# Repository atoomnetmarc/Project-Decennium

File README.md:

# Status

Assembled and working.

# Firmware

Flash the firmware: https://github.com/atoomnetmarc/Project-Decennium-Firmware

# Build

Order components mentioned on the [BOM](Kicad/bom/ibom.html). For the `Wemos D1 mini usb-c` (U1) you need 2 pieces of 1x08 right angle 2.54mm pin header.

Order PCB. You may want to check the option remove the order number from the front of the PCB.

Solder the PCB.

# 3d-print

3d-print a [stand](3d-print/Project-Decennium%20PCB%20stand.stl). Orient the print for printing like [this](3d-print/Project-Decennium%20PCB%20stand%20-%20print%20orientation%20example.png).

Use 2 M3x12 BHCS screws to screw the stand to the pcb.

# Pics

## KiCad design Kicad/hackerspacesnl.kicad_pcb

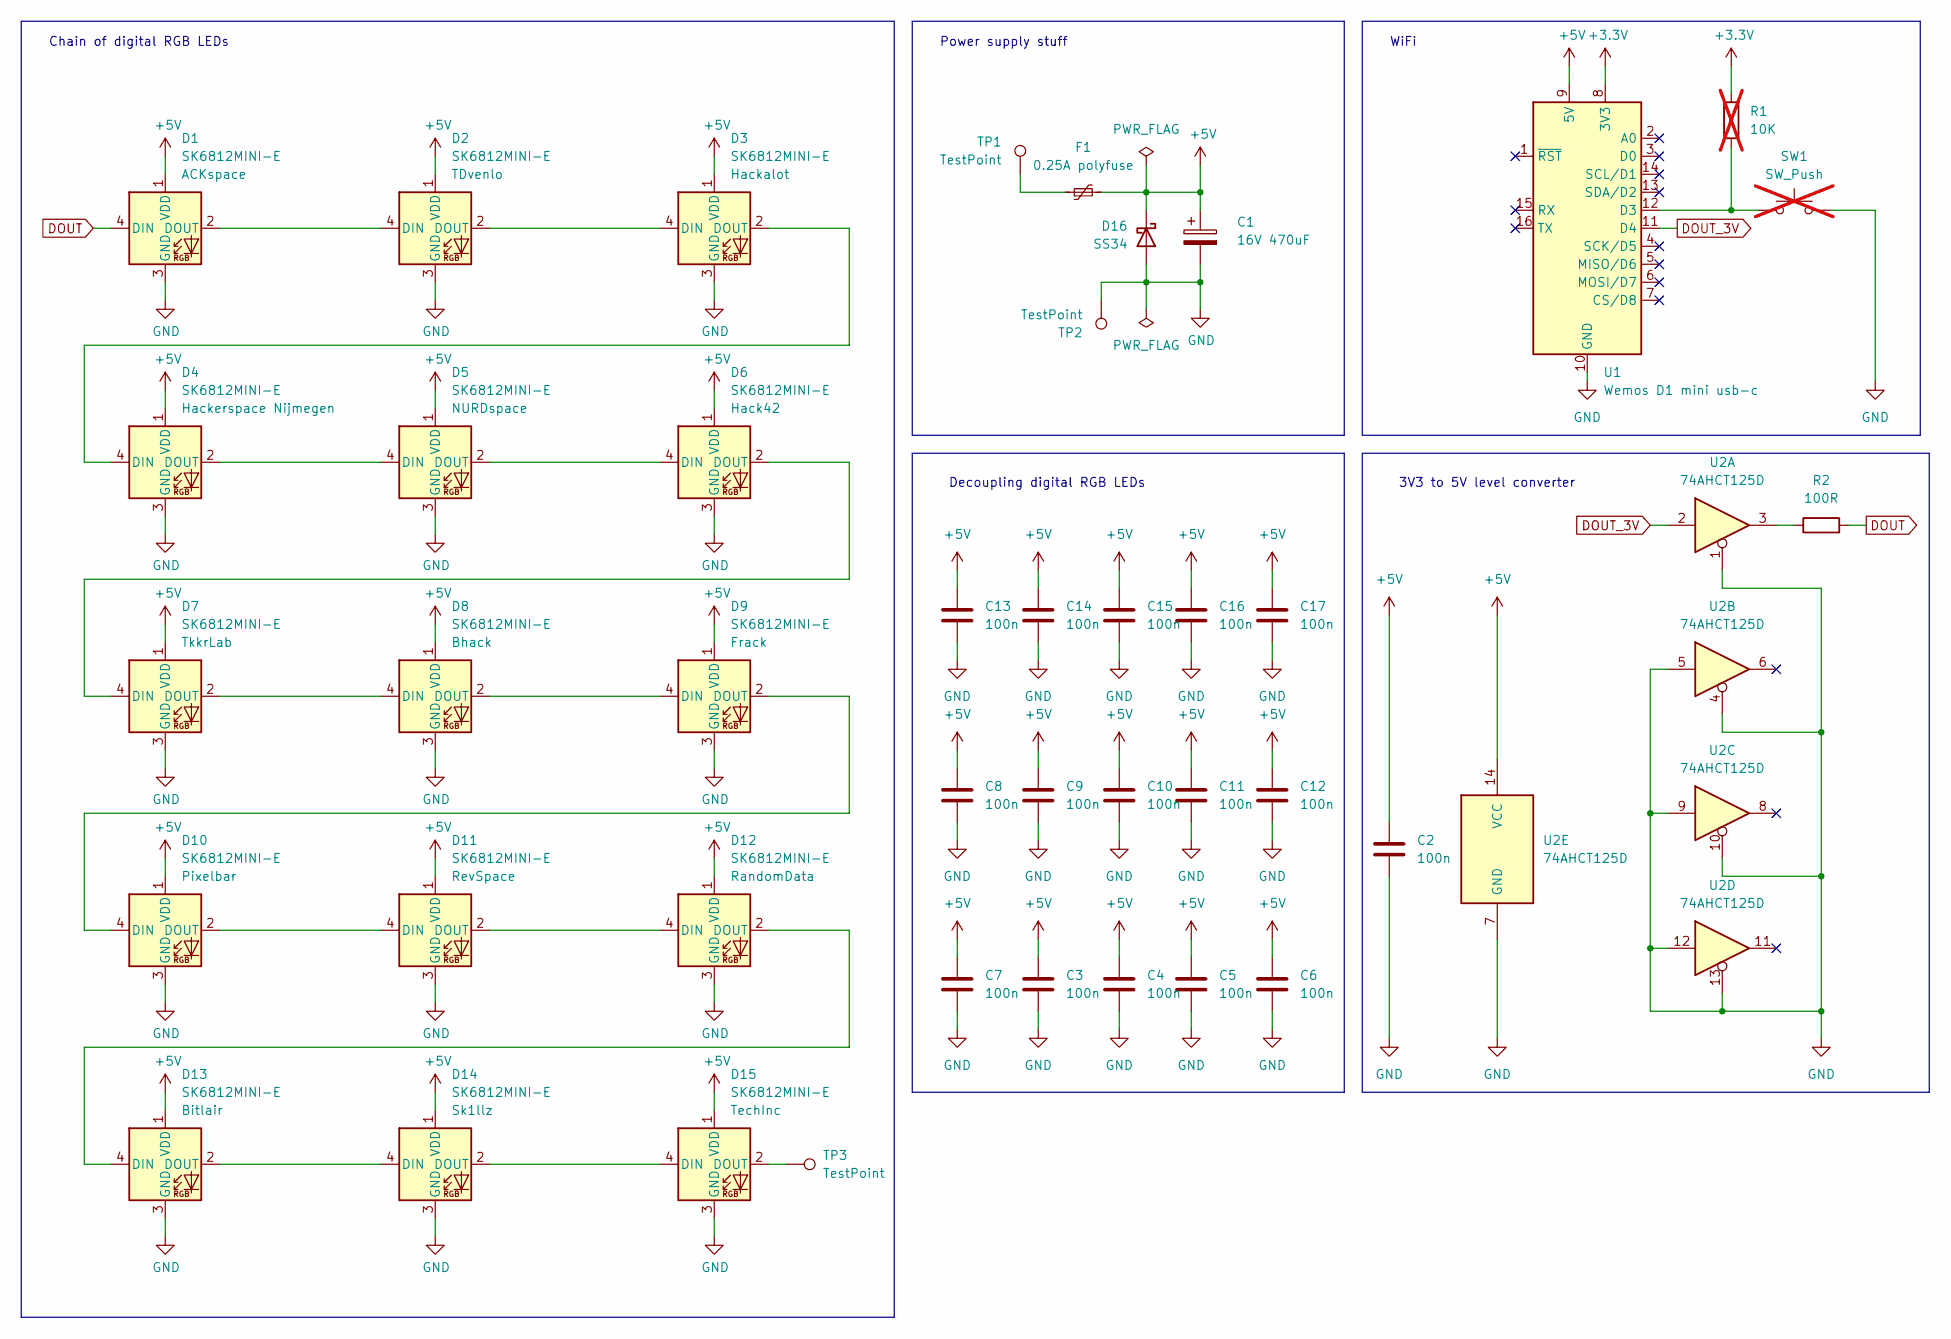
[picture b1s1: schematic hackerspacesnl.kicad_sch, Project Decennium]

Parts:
C1: 16V 470uF; CP_Elec_10x10.5
C2, C3, C4, C5, C6, C7, C8, C9, C10, C11, C12, C13, C14, C15, C16, C17: 100n; C_0805_2012Metric_Pad1.18x1.45mm_HandSolder
D1, D2, D3, D4, D5, D6, D7, D8, D9, D10, D11, D12, D13, D14, D15: SK6812MINI-E; LED_SK6812MINI-E_3.2x2.8x1.78mm_P1.5mm; LCSC C391863
D16: SS34; D_SMA
F1: 0.25A polyfuse; Fuse_1206_3216Metric_Pad1.42x1.75mm_HandSolder
R1: 10K; R_0805_2012Metric_Pad1.20x1.40mm_HandSolder; not fitted
R2: 100R; R_0805_2012Metric_Pad1.20x1.40mm_HandSolder
SW1: SW_Push; SW_SPST_CK_RS282G05A3; not fitted
TP1, TP2: TestPoint; TestPoint_Pad_D4.0mm
TP3: TestPoint; TestPoint_Pad_D1.5mm
U1: Wemos D1 mini usb-c; WEMOS_D1_mini_smt_hack
U2: 74AHCT125D; SOIC-14_3.9x8.7mm_P1.27mm

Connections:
+3.3V: R1.2, U1.8 (3V3)
+5V: C1.1, C2.1, C3.1, C4.1, C5.1, C6.1, C7.1, C8.1, C9.1, C10.1, C11.1, C12.1, C13.1, C14.1, C15.1, C16.1, C17.1, D1.1 (VDD), D2.1 (VDD), D3.1 (VDD), D4.1 (VDD), D5.1 (VDD), D6.1 (VDD), D7.1 (VDD), D8.1 (VDD), D9.1 (VDD), D10.1 (VDD), D11.1 (VDD), D12.1 (VDD), D13.1 (VDD), D14.1 (VDD), D15.1 (VDD), D16.1 (K), F1.2, U1.9 (5V), U2.14 (VCC)
DOUT: D1.4 (DIN), R2.2
DOUT_3V: U1.11 (D4), U2.2
GND: C1.2, C2.2, C3.2, C4.2, C5.2, C6.2, C7.2, C8.2, C9.2, C10.2, C11.2, C12.2, C13.2, C14.2, C15.2, C16.2, C17.2, D1.3 (GND), D2.3 (GND), D3.3 (GND), D4.3 (GND), D5.3 (GND), D6.3 (GND), D7.3 (GND), D8.3 (GND), D9.3 (GND), D10.3 (GND), D11.3 (GND), D12.3 (GND), D13.3 (GND), D14.3 (GND), D15.3 (GND), D16.2 (A), SW1.1, TP2.1, U1.10 (GND), U2.1, U2.4, U2.5, U2.7 (GND), U2.9, U2.10, U2.12, U2.13
unnamed: D1.2 (DOUT), D2.4 (DIN)
unnamed: D2.2 (DOUT), D3.4 (DIN)
unnamed: D3.2 (DOUT), D4.4 (DIN)
unnamed: D4.2 (DOUT), D5.4 (DIN)
unnamed: D5.2 (DOUT), D6.4 (DIN)
unnamed: D6.2 (DOUT), D7.4 (DIN)
unnamed: D7.2 (DOUT), D8.4 (DIN)
unnamed: D8.2 (DOUT), D9.4 (DIN)
unnamed: D9.2 (DOUT), D10.4 (DIN)
unnamed: D10.2 (DOUT), D11.4 (DIN)
unnamed: D11.2 (DOUT), D12.4 (DIN)
unnamed: D12.2 (DOUT), D13.4 (DIN)
unnamed: D13.2 (DOUT), D14.4 (DIN)
unnamed: D14.2 (DOUT), D15.4 (DIN)
unnamed: D15.2 (DOUT), TP3.1
unnamed: F1.1, TP1.1
unnamed: R2.1, U2.3
unnamed: R1.1, SW1.2, U1.12 (D3)

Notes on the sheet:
3V3 to 5V level converter
Power supply stuff
WiFi
Decoupling digital RGB LEDs
Chain of digital RGB LEDs

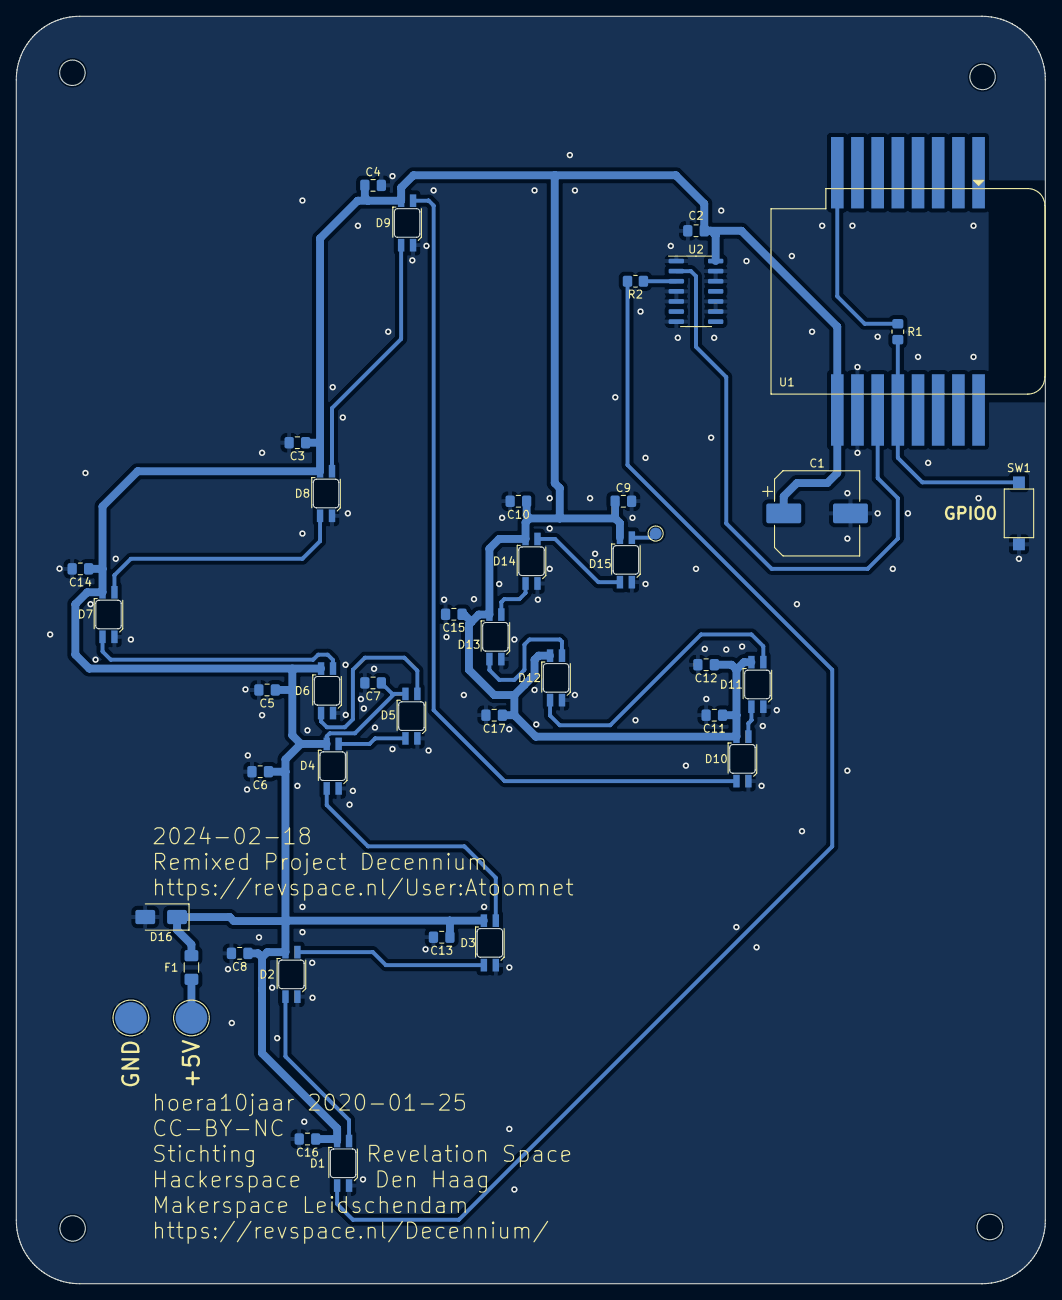
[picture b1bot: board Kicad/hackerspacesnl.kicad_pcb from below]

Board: 2 copper layers, 129.5 x 159.5 mm, 44 parts (43 on the bottom side), 23 nets.

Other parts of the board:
Ref**: Val**; hsnl
Ref**#2: Val**; revspace_logo

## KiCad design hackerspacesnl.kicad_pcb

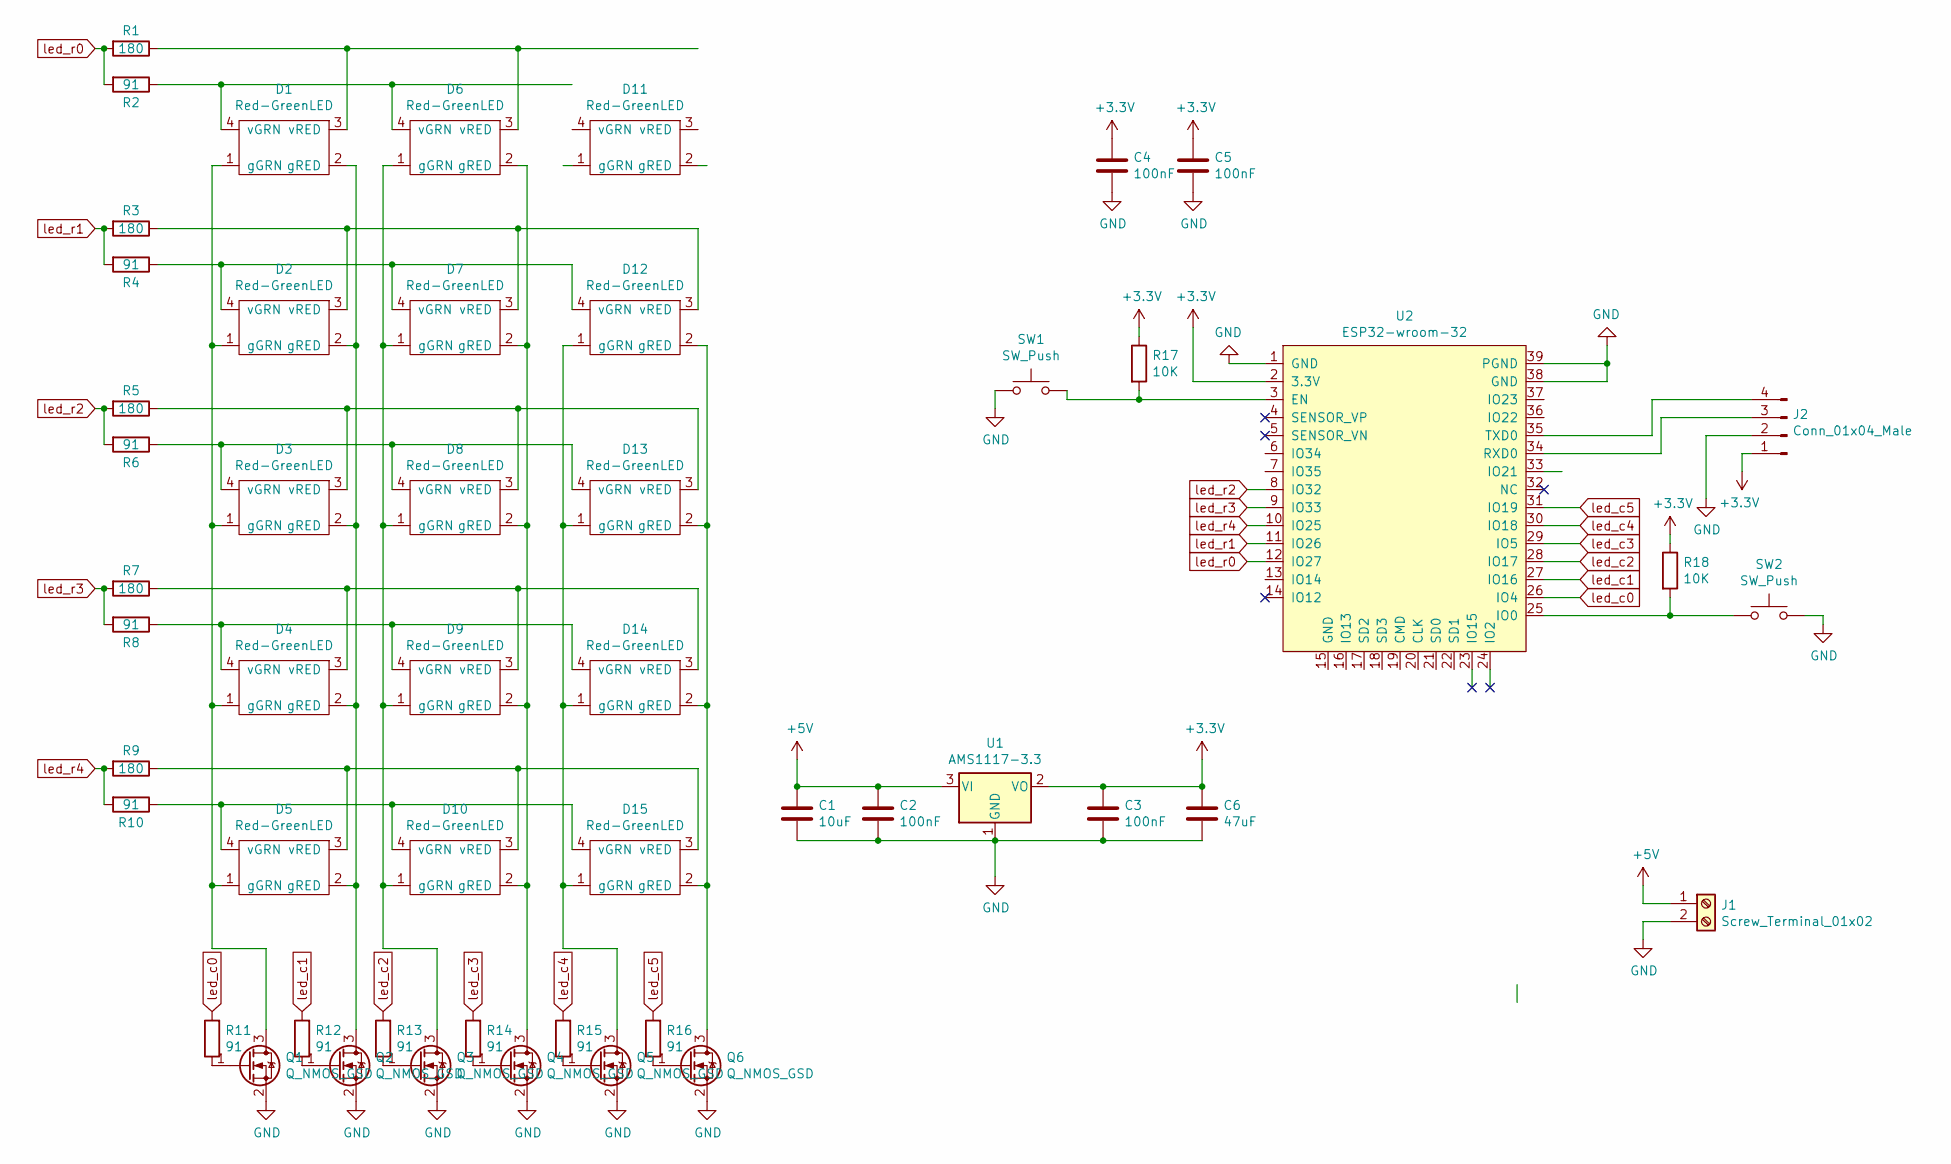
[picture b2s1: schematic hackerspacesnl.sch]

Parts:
C1: 10uF; C_0603_1608Metric; LCSC C19702
C2, C3, C4, C5: 100nF; C_0603_1608Metric; LCSC C14663
C6: 47uF; C_0805_2012Metric; LCSC C16780
D1, D2, D3, D4, D5, D6, D7, D8, D9, D10, D11, D12, D13, D14, D15: Red-GreenLED; LED_0805_multicolor; LCSC C391863
J1: Screw_Terminal_01x02; PhoenixContact_MSTBA_2,5_2-G-5,08_1x02_P5.08mm_Horizontal
J2: Conn_01x04_Male; PinHeader_1x04_P2.54mm_Vertical
Q1, Q2, Q3, Q4, Q5, Q6: Q_NMOS_GSD; SOT-23; LCSC C181087
R1, R3, R5, R7, R9: 180; R_0603_1608Metric; LCSC C22828
R2, R4, R6, R8, R10, R11, R12, R13, R14, R15, R16: 91; R_0603_1608Metric; LCSC C25199
R17, R18: 10K; R_0603_1608Metric; LCSC C25804
SW1, SW2: SW_Push; SW_SPST_TL3342
U1: AMS1117-3.3; SOT-223-3_TabPin2; LCSC C6186
U2: ESP32-wroom-32; ESP32-WROOM-32

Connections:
+3V3: C3.1, C4.1, C5.1, C6.1, J2.1, R17.1, R18.1, U1.2 (VO), U2.2 (3.3V)
+5V: C1.1, C2.1, J1.1, U1.3 (VI)
GND: C1.2, C2.2, C3.2, C4.2, C5.2, C6.2, J1.2, J2.2, Q1.2 (S), Q2.2 (S), Q3.2 (S), Q4.2 (S), Q5.2 (S), Q6.2 (S), SW1.1, SW2.2, U1.1 (GND), U2.1 (GND), U2.38 (GND), U2.39 (PGND)
unnamed: D1.1 (gGRN), D2.1 (gGRN), D3.1 (gGRN), D4.1 (gGRN), D5.1 (gGRN), Q1.3 (D)
unnamed: D1.2 (gRED), D2.2 (gRED), D3.2 (gRED), D4.2 (gRED), D5.2 (gRED), Q2.3 (D)
unnamed: D1.3 (vRED), D6.3 (vRED), R1.1
unnamed: D1.4 (vGRN), D6.4 (vGRN), R2.1
unnamed: D6.1 (gGRN), D7.1 (gGRN), D8.1 (gGRN), D9.1 (gGRN), D10.1 (gGRN), Q3.3 (D)
unnamed: D6.2 (gRED), D7.2 (gRED), D8.2 (gRED), D9.2 (gRED), D10.2 (gRED), Q4.3 (D)
unnamed: D5.3 (vRED), D10.3 (vRED), D15.3 (vRED), R9.1
unnamed: D5.4 (vGRN), D10.4 (vGRN), D15.4 (vGRN), R10.1
unnamed: D12.1 (gGRN), D13.1 (gGRN), D14.1 (gGRN), D15.1 (gGRN), Q5.3 (D)
unnamed: D12.2 (gRED), D13.2 (gRED), D14.2 (gRED), D15.2 (gRED), Q6.3 (D)
unnamed: D2.3 (vRED), D7.3 (vRED), D12.3 (vRED), R3.1
unnamed: D2.4 (vGRN), D7.4 (vGRN), D12.4 (vGRN), R4.1
unnamed: D3.3 (vRED), D8.3 (vRED), D13.3 (vRED), R5.1
unnamed: D3.4 (vGRN), D8.4 (vGRN), D13.4 (vGRN), R6.1
unnamed: D4.3 (vRED), D9.3 (vRED), D14.3 (vRED), R7.1
unnamed: D4.4 (vGRN), D9.4 (vGRN), D14.4 (vGRN), R8.1
unnamed: J2.3, U2.34 (RXD0)
unnamed: J2.4, U2.35 (TXD0)
unnamed: Q1.1 (G), R11.1
unnamed: Q2.1 (G), R12.1
unnamed: Q3.1 (G), R13.1
unnamed: Q4.1 (G), R14.1
unnamed: Q5.1 (G), R15.1
unnamed: Q6.1 (G), R16.1
unnamed: R17.2, SW1.2, U2.3 (EN)
unnamed: R18.2, SW2.1, U2.25 (IO0)
led_c0: R11.2, U2.26 (IO4)
led_c1: R12.2, U2.27 (IO16)
led_c2: R13.2, U2.28 (IO17)
led_c3: R14.2, U2.29 (IO5)
led_c4: R15.2, U2.30 (IO18)
led_c5: R16.2, U2.31 (IO19)
led_r0: R1.2, R2.2, U2.12 (IO27)
led_r1: R3.2, R4.2, U2.11 (IO26)
led_r2: R5.2, R6.2, U2.8 (IO32)
led_r3: R7.2, R8.2, U2.9 (IO33)
led_r4: R9.2, R10.2, U2.10 (IO25)

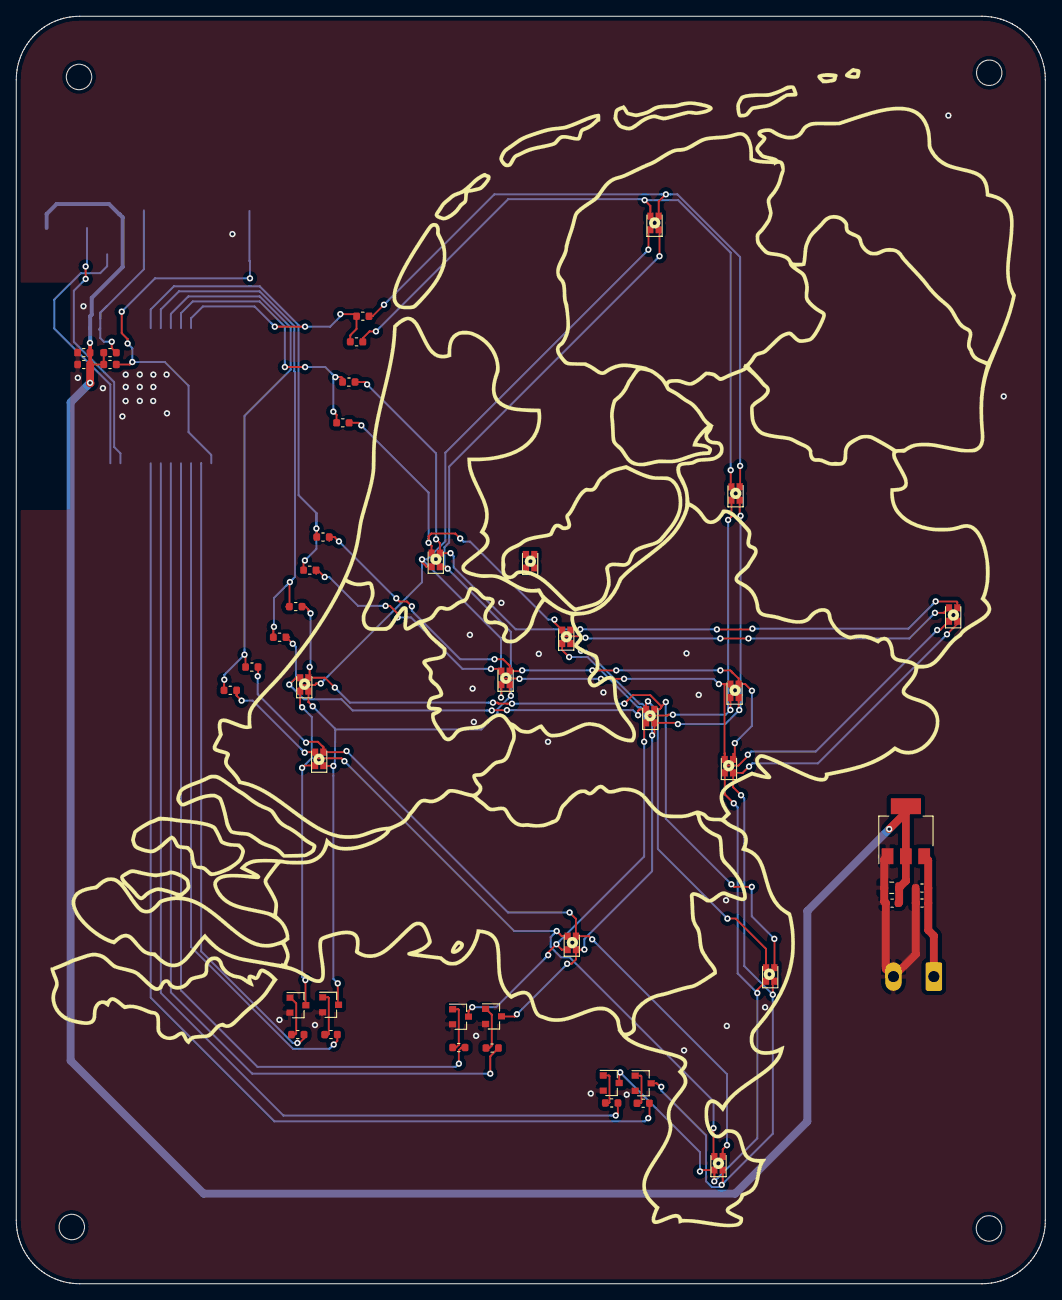
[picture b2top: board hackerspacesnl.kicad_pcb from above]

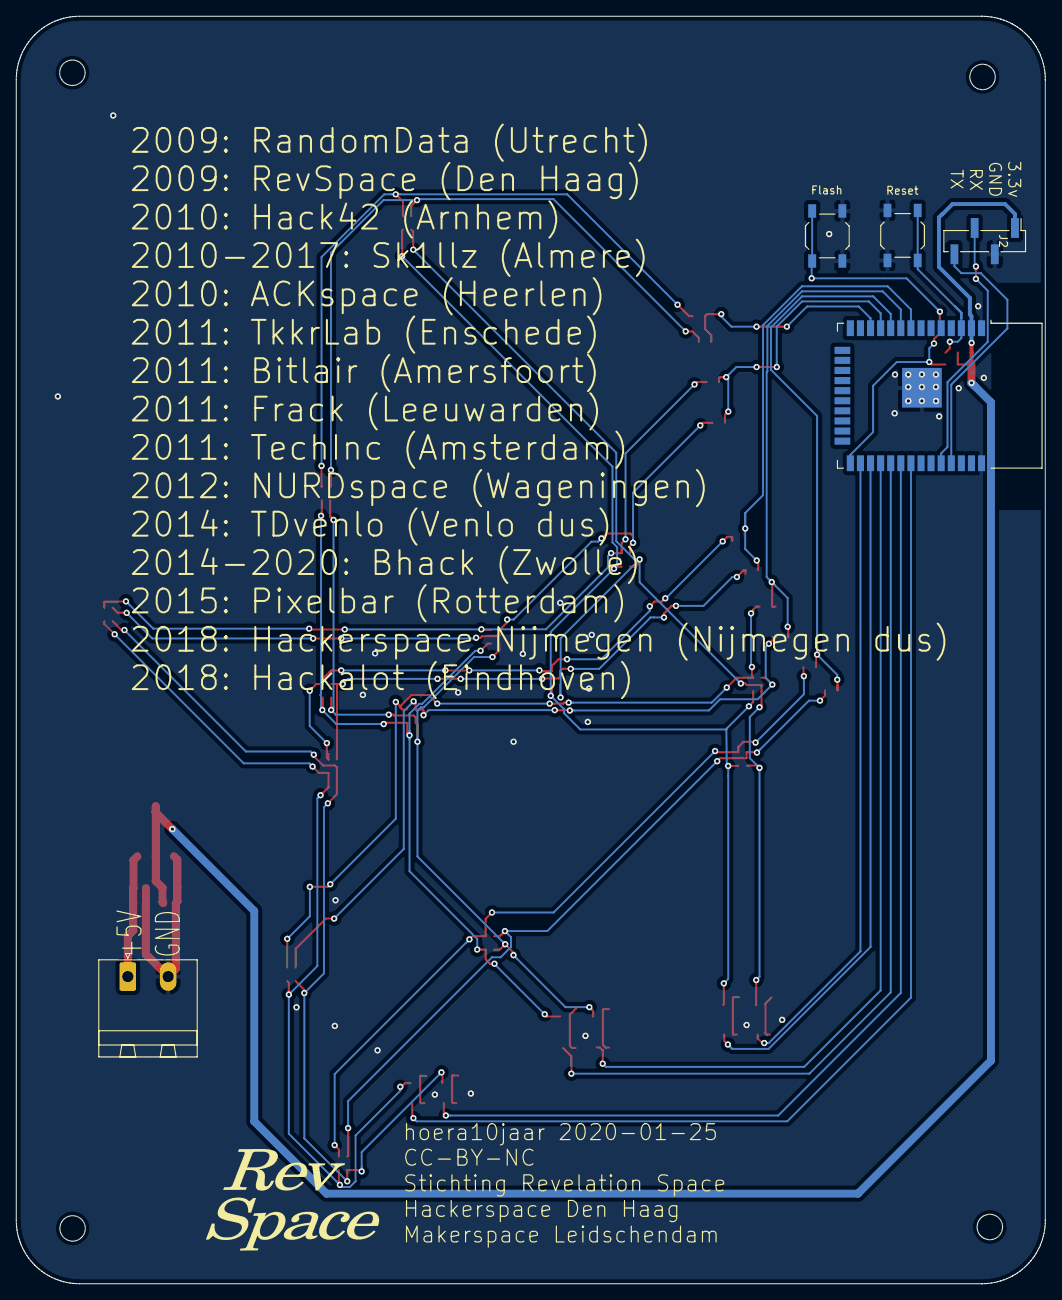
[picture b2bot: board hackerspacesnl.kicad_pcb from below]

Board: 2 copper layers, 129.5 x 159.5 mm, 53 parts (6 on the bottom side), 40 nets.

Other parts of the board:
Ref**: Val**; revspace_logo
Ref**#2: Val**; hsnl

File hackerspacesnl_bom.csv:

"Id";"Designator";"Behuizing";"Hoeveelheid";"Orientatie";"Leverancier en ref";
1;"Ref**";"hsnl";1;"Val**";;;
2;"Ref**";"revspace_logo";1;"Val**";;;
3;"REF**,REF**,REF**,REF**";"MountingHole_3.2mm_M3";4;"MountingHole_3.2mm_M3";;;
4;"J2";"PinHeader_1x04_P2.54mm_Vertical_SMD_Pin1Left";1;"Conn_01x04_Male";;;
5;"R17,R18";"R_0603_1608Metric";2;"10K";;;
6;"D8,D9,D12,D15,D14,D13,D11,D10,D7,D6,D5,D4,D3,D2,D1";"LED_0805_multicolor";15;"Red-GreenLED";;;
7;"U2";"ESP32-WROOM-32";1;"ESP32-wroom-32";;;
8;"U1";"SOT-223-3_TabPin2";1;"AMS1117-3.3";;;
9;"SW2,SW1";"SW_SPST_TL3342";2;"SW_Push";;;
10;"R16,R15,R14,R13,R12,R11,R10,R8,R6,R4,R2";"R_0603_1608Metric";11;"91";;;
11;"R9,R7,R5,R3,R1";"R_0603_1608Metric";5;"180";;;
12;"Q6,Q5,Q4,Q3,Q2,Q1";"SOT-23";6;"Q_NMOS_GSD";;;
13;"C6";"C_0805_2012Metric";1;"47uF";;;
14;"C5,C4,C3,C2";"C_0603_1608Metric";4;"100nF";;;
15;"C1";"C_0603_1608Metric";1;"10uF";;;
16;"J1";"PhoenixContact_MSTBA_2,5_2-G-5,08_1x02_P5.08mm_Horizontal";1;"Screw_Terminal_01x02";;;

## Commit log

2019-12-20 add values, connect matrix
2019-12-20 schema compleet
2019-12-20 art silk and board outline
2019-12-21 schemafoutje gefixt en eerste pcb stapjes
2019-12-21 led footprint
2019-12-21 board outline
2019-12-21 fixed LED symbol, began initial layout
2019-12-21 wat moves
2019-12-21 sorted ratsnest, removed map as we will go bigger
2019-12-22 nieuwe svg voor hsnl
2019-12-22 nieuwe HSNL kaart en mod
2019-12-22 bezig met nieuwe kaart, leds geplaatst en test van traces
2019-12-22 halverwege component plaatsing
2019-12-22 update multicolor led pads
2019-12-23 layout almost done
2019-12-23 back silk text and holes added
2019-12-23 klaar op refs na
2019-12-23 klaar?
2019-12-23 opgeruimd
2019-12-23 production files
2019-12-23 wrong capacitor in BOM
2019-12-23 fixed hsnl map footprint from uglies and generated new gerbers
2019-12-23 silkscreen and new gerbers
2019-12-23 versie zoals besteld
2019-12-24 corrected POS excel document, added JLCpcb renders of P&P
2020-01-04 nieuwe rev
2020-01-18 laatste
2024-02-18 Remix design. Use Wemos D1 mini and SK6812 instead of ESP32 with RG-led matrix.
2024-02-18 Case correct.
2024-02-23 Add link to firmware.
2024-02-25 Add 3d-printable stand.
2024-02-29 Add photos off assembled PCB.
2024-03-01 Add 2 ty-rap holes.
2024-10-12 Add ordering hints.
2026-01-23 Add CONTRIBUTING.md

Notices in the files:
Kicad/hackerspacesnl.kicad_pcb:
CC-BY-NC
